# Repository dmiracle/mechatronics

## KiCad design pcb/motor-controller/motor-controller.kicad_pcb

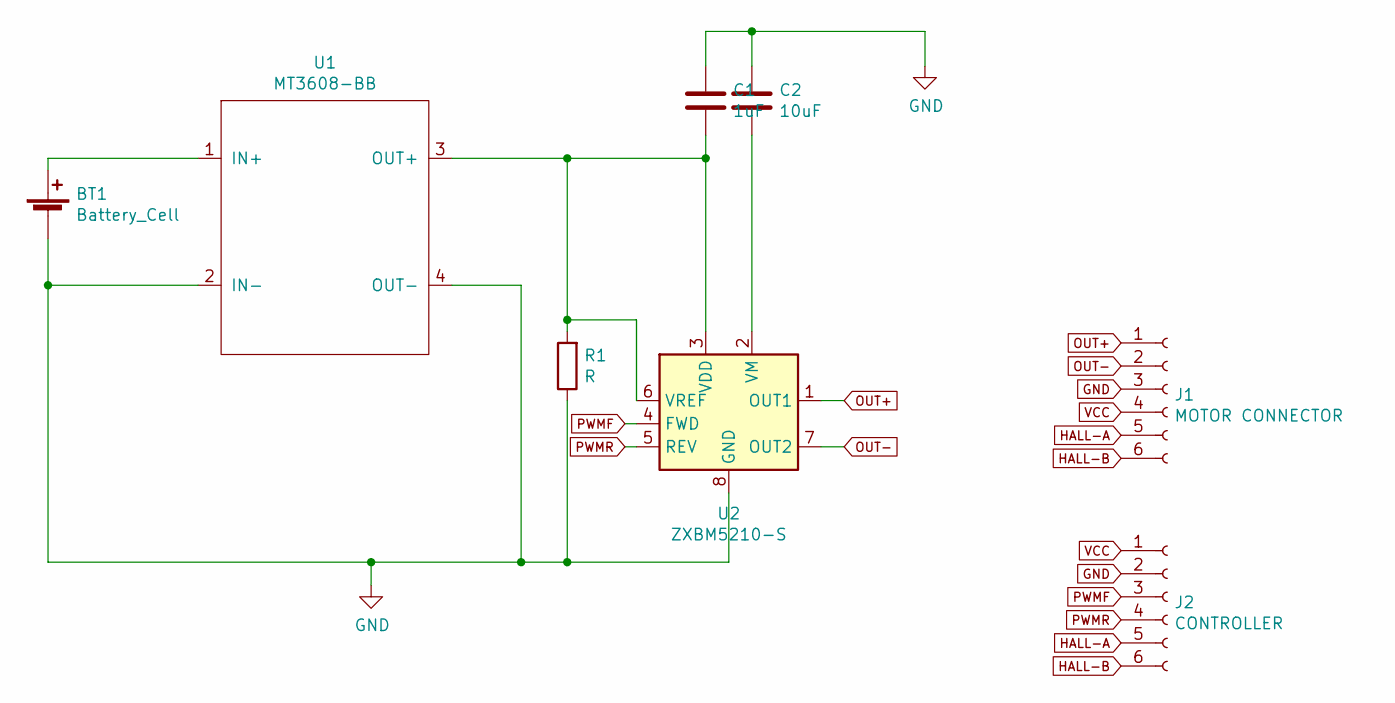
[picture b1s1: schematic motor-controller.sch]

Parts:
BT1: Battery_Cell; M65P25-1011
C1: 1uF; C_0805_2012Metric_Pad1.15x1.40mm_HandSolder
C2: 10uF; C_0805_2012Metric_Pad1.15x1.40mm_HandSolder
J1: MOTOR CONNECTOR; PinHeader_1x06_P2.54mm_Vertical
J2: CONTROLLER; PinHeader_1x06_P2.54mm_Vertical
R1: R; R_0805_2012Metric_Pad1.15x1.40mm_HandSolder
U1: MT3608-BB
U2: ZXBM5210-S; SOIC-8_3.9x4.9mm_P1.27mm

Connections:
GND: BT1.2 (-), C1.1, C2.1, J1.3, J2.2, R1.1, U1.2 (IN-), U1.4 (OUT-), U2.8 (GND)
HALL-A: J1.5, J2.5
HALL-B: J1.6, J2.6
unnamed: BT1.1 (+), U1.1 (IN+)
unnamed: C1.2, R1.2, U1.3 (OUT+), U2.3 (VDD), U2.6 (VREF)
unnamed: C2.2, U2.2 (VM)
OUT+: J1.1, U2.1 (OUT1)
OUT-: J1.2, U2.7 (OUT2)
PWMF: J2.3, U2.4 (FWD)
PWMR: J2.4, U2.5 (REV)
VCC: J1.4, J2.1

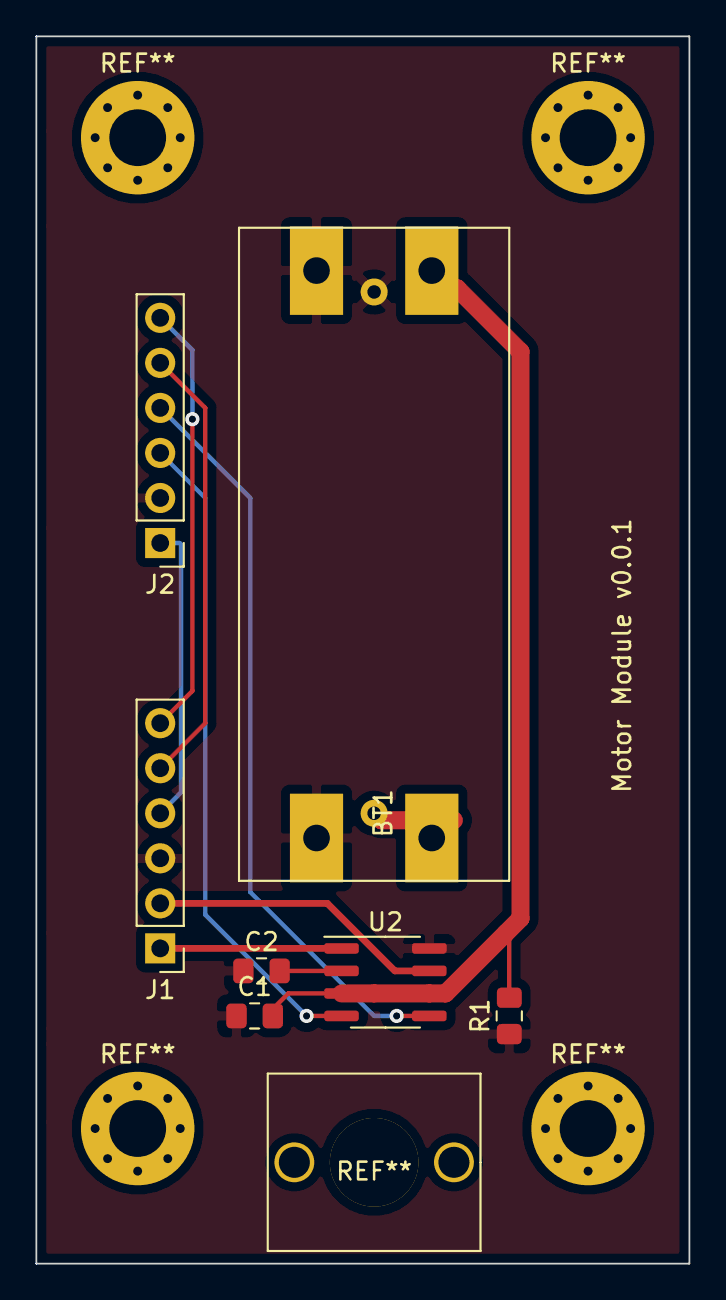
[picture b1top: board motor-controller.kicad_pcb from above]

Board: 2 copper layers, 36.8 x 69.2 mm, 8 parts (1 on the bottom side), 11 nets.

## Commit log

2020-09-27 init
